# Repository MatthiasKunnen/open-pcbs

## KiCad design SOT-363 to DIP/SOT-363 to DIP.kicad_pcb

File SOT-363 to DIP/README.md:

# Adapter PCB for 0.65 mm pitch, 6 pin components to DIP-6
keywords: TSSOP-5, SOT-353, TSSOP-6, SOT-363

Made specifically for [SOT-353](https://www.nxp.com/docs/en/package-information/SOT353-1.pdf) and [SOT-363](https://www.nxp.com/docs/en/package-information/SOT363.pdf).

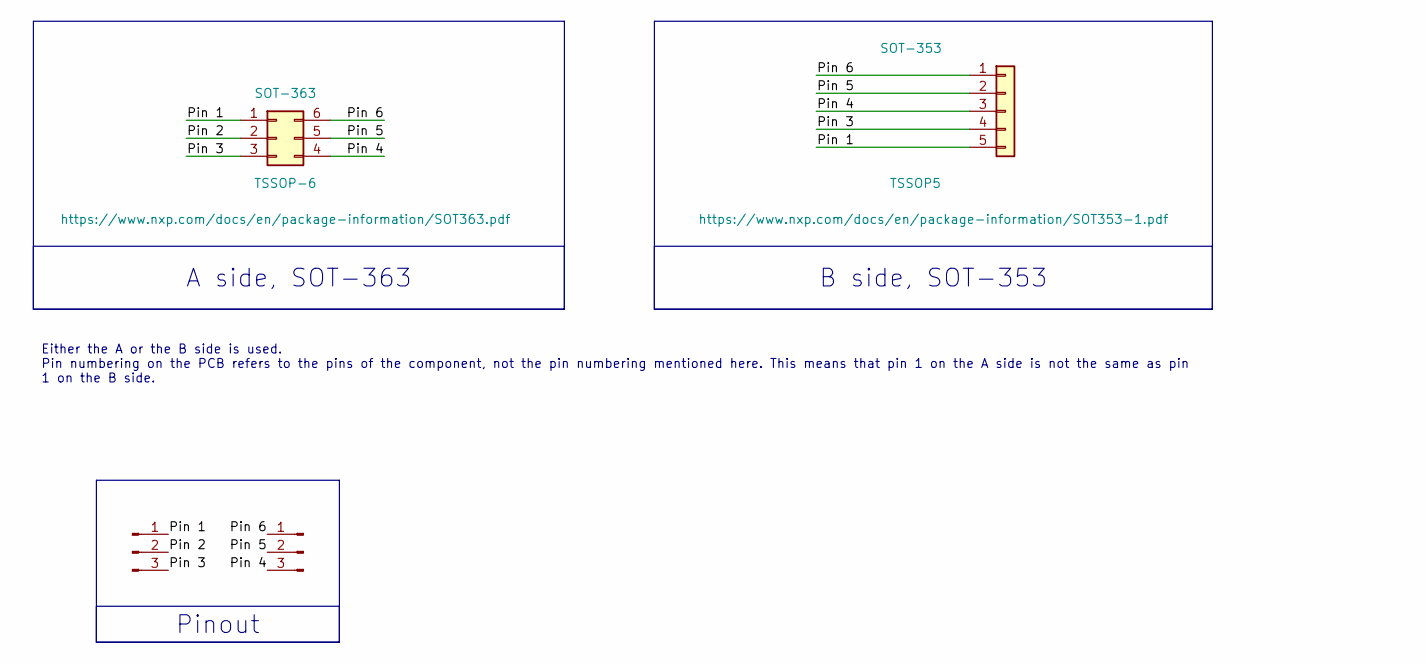
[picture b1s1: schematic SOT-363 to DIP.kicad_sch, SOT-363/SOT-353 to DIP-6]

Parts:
J1: SOT-363; SOT-363_SC-70-6_Handsoldering
J2, J3: Conn_01x03_Pin; PinHeader_1x03_P2.54mm_Vertical_nosilk
J4: SOT-353; SOT-353_SC-70-5_Handsoldering

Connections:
/Pin 1: J1.1, J2.1, J4.5
/Pin 2: J1.2, J2.2
/Pin 3: J1.3, J2.3, J4.4
/Pin 4: J1.4, J3.3, J4.3
/Pin 5: J1.5, J3.2, J4.2
/Pin 6: J1.6, J3.1, J4.1

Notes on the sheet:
B side, SOT-353
A side, SOT-363
Pinout
Either the A or the B side is used. Pin numbering on the PCB refers to the pins of the component, not the pin numbering mentioned here. This means that pin 1 on the A side is not the same as pin 1 on the B side.

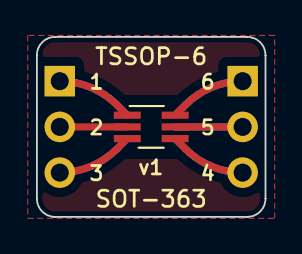
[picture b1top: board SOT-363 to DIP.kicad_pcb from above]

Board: 2 copper layers, 12.7 x 10.0 mm, 4 parts (1 on the bottom side), 6 nets.

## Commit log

2023-10-27 Create SOT-353/363 to DIP-6 adapter
2023-10-27 Remove silkscreen of pin headers
2023-10-27 Decrease height to 10mm
